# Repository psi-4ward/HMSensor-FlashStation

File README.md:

# HMSensor-FlashStation

Hilfsplatine um HMSensor PCBs mit Hilfe von PogoPins einzuspannend und zu flashen.

HMSensor versucht eine universelle Hardware-Basis für AskSin++ Sensoren und Aktoren zu sein.

* [HMSensor PCB](https://github.com/pa-pa/HMSensor) from pa-pa
* [HMSensor Documentation](https://asksinpp.de/Projekte/psi/HMSensor/) on asksinpp.de

Auf dem Testaufbau sind **P75-B1 Pogo Pins** verbaut.

## :bangbang::bug: **Fehler in v1.0** :bangbang:

* RX/TX ist _nicht_ gedreht gegenüber dem USB-UART. Entweder FTDI über JumperWire anschließen und RX/TX drehen oder den Fehler mit Draht auf der Platine beheben.
* RESET Kondensator fehlt

=> [v1.0 BugFix Guide](./v1.0-bugfix-guide/README.md)

## Features

* DIP-Schalter um die Versorgungsspannungen zu schalten.
* VCC-Jumper: z.B. um eine Strommessung zwischen zu schalten.
* 5x2 Pin ISP Header, kompatibel mit Diamex oder USBasp
* FTDI Header

## Changelog / Notes

### v1.1

* Fehler Behoben im PCB-Design: RX/TX ist _nicht_ gedreht gegenüber dem USB-UART
* RESET Kondensator hinzugefügt

## Lizenz

MIT

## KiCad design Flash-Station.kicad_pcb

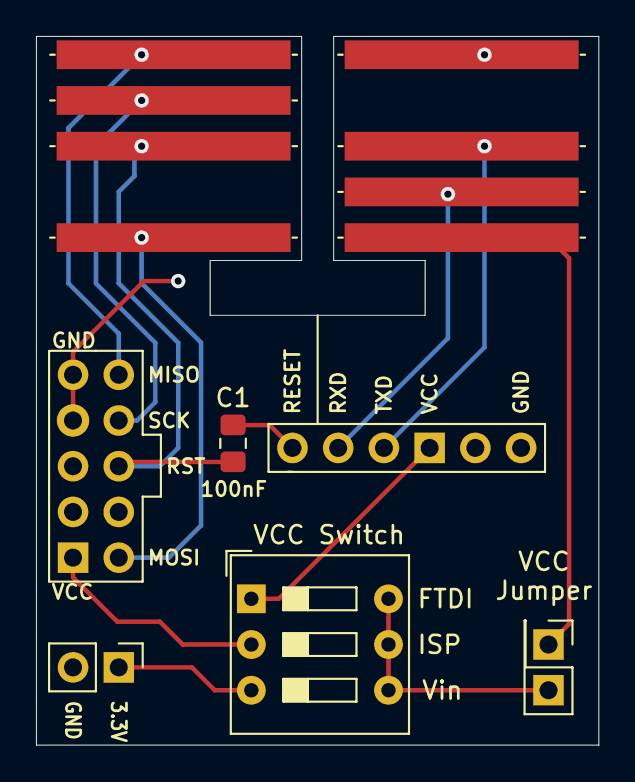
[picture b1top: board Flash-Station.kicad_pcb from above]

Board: 2 copper layers, 31.2 x 39.4 mm, 8 parts (0 on the bottom side), 13 nets.

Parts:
C1: 100nF; C_0805_2012Metric_Pad1.15x1.40mm_HandSolder
J1: Vin 3.3V; PinHeader_1x02_P2.54mm_Vertical
J2: FTDI; PinHeader_1x06_P2.54mm_Vertical
J3: ISP; PinHeader_2x05_P2.54mm_Vertical
J4: HMSensor Pogo 2; PogoPad_5x
J5: HMSensor Pogo 1; PogoPad_5x
J6: VCC Jumper; PinHeader_2x01_P2.54mm_Vertical
SW1: VCC Switch; SW_DIP_SPSTx03_Slide_9.78x9.8mm_W7.62mm_P2.54mm

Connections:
GND: J1.2, J2.6, J3.1, J3.3, J4.1
MISO: J3.2, J5.5
MOSI: J3.10, J5.1
unnamed: C1.1, J2.1
unnamed: J1.1, SW1.3
unnamed: J2.4, SW1.1
unnamed: J3.9, SW1.2
unnamed: J4.5, J6.1
RESET: C1.2, J3.6, J5.3
RXD: J2.3, J4.3
SCK: J3.4, J5.4
TXD: J2.2, J4.4
VCC: J6.2, SW1.4, SW1.5, SW1.6

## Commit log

2020-03-07 init
2020-03-08 Update gitignore
2020-03-08 Fix: Tx/RX interchanged, RESET Kerko
2020-03-08 Add v1.2 PCB image
2020-03-08 Resize PCB image
2020-03-08 Updated sch
2020-03-08 Add v1.0 Bugfix guide
2020-03-09 Fix Schaltplan
2020-04-13 Fix gerber
2020-04-13 Fix plot settings
